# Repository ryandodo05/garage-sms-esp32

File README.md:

# Projet : Carte ESP32 + SIM7080G, pilotage d'une porte de garage par SMS

Carte PCB ESP32 avec module SIM7080G, relais et capteur ultrason, pour surveiller
et piloter une porte de garage par SMS.

Auteur : Ryan, https://ryan-dodo.be/Projet1.html

## Description

Le but du projet est de surveiller et piloter à distance plusieurs éléments de mon
domicile, principalement ma porte de garage. Le cœur de la carte est un ESP32,
complété par un module SIM7080G qui assure la communication cellulaire par SMS.

- **Porte de garage** : une broche de l'ESP32 est reliée à l'entrée du boîtier de
  gestion de la porte. Un SMS contenant « Garage » envoie une impulsion : si la
  porte est fermée, elle s'ouvre, et inversement.
- **Détection de voiture** : un capteur ultrason HC-SR04 (portée d'environ 5 mètres)
  est fixé au mur du garage. En réponse au SMS « Garage », il indique si une voiture
  est garée ou non.
- **Pilotage de charges** : deux relais permettent de commuter du 12 V. Comme la
  sortie de l'ESP32 ne fournit pas assez de tension ni de courant pour la bobine,
  chaque relais est commandé par un transistor et des résistances. Un SMS tel que
  « relai1 » active le relais 1, par exemple pour alimenter un spot LED.
- **Sécurité** : seuls les SMS envoyés depuis mon numéro de téléphone sont pris en
  compte. Tout message provenant d'un autre numéro est ignoré.

## Fonctionnalités

- Ouverture / fermeture de la porte de garage par SMS (impulsion sur broche dédiée)
- Détection de présence de voiture par capteur ultrason HC-SR04 (~5 m)
- Réponse par SMS : voiture garée ou garage libre
- Commande de deux relais 12 V par SMS (ex. « relai1 », « relai2 »)
- Commande des relais via transistors et résistances de base
- Filtrage des commandes : acceptées uniquement depuis mon numéro
- Communication cellulaire LTE-M avec le module SIM7080G
- PCB conçue entièrement par mes soins sous Eagle

## Caractéristiques

| Élément | Détail |
|---|---|
| Microcontrôleur | ESP32 |
| Communication | SIM7080G (LTE-M uniquement) |
| Sorties | 2 relais 12 V, pilotés par transistor |
| Capteur | HC-SR04, portée ~5 m |
| Commande porte | Impulsion sur broche dédiée |
| Conception | PCB dessinée par mes soins, fabriquée chez JLCPCB |

## Conception & fabrication

La carte a été entièrement conçue par mes soins sous Eagle (schéma, placement et
routage). Les fichiers Gerber ont été exportés puis la carte est fabriquée chez
JLCPCB, afin de limiter au maximum le risque de défaut de fabrication.

## Coûts indicatifs

| Élément | Prix |
|---|---|
| ESP32 | 13 € |
| Relais (unité) | 3 € |
| Module SIM7080G | 56 € |
| Reste des composants (transistors, résistances, capteur HC-SR04, connecteurs, PCB…) | 30 à 40 € |
| Abonnement SIM Orange (LTE-M), SMS illimités entrants et sortants | 15 € / mois |

La SIM doit être en LTE-M, car le module SIM7080G n'accepte que cette technologie.
Le forfait choisi permet d'envoyer et de recevoir autant de messages que souhaité.

## Vue 3D de la PCB

Voir la vue 3D interactive (chargement des Gerbers) sur
https://ryan-dodo.be/Projet1.html

<!--  -->

## Défis rencontrés

Le placement des composants RF du SIM7080G (antenne, découplage, masse) a demandé
une attention particulière pour limiter les interférences avec le reste de la carte.
La commande des relais 12 V a également nécessité l'ajout de transistors, car la
sortie de l'ESP32 ne suffit pas à alimenter directement les bobines.

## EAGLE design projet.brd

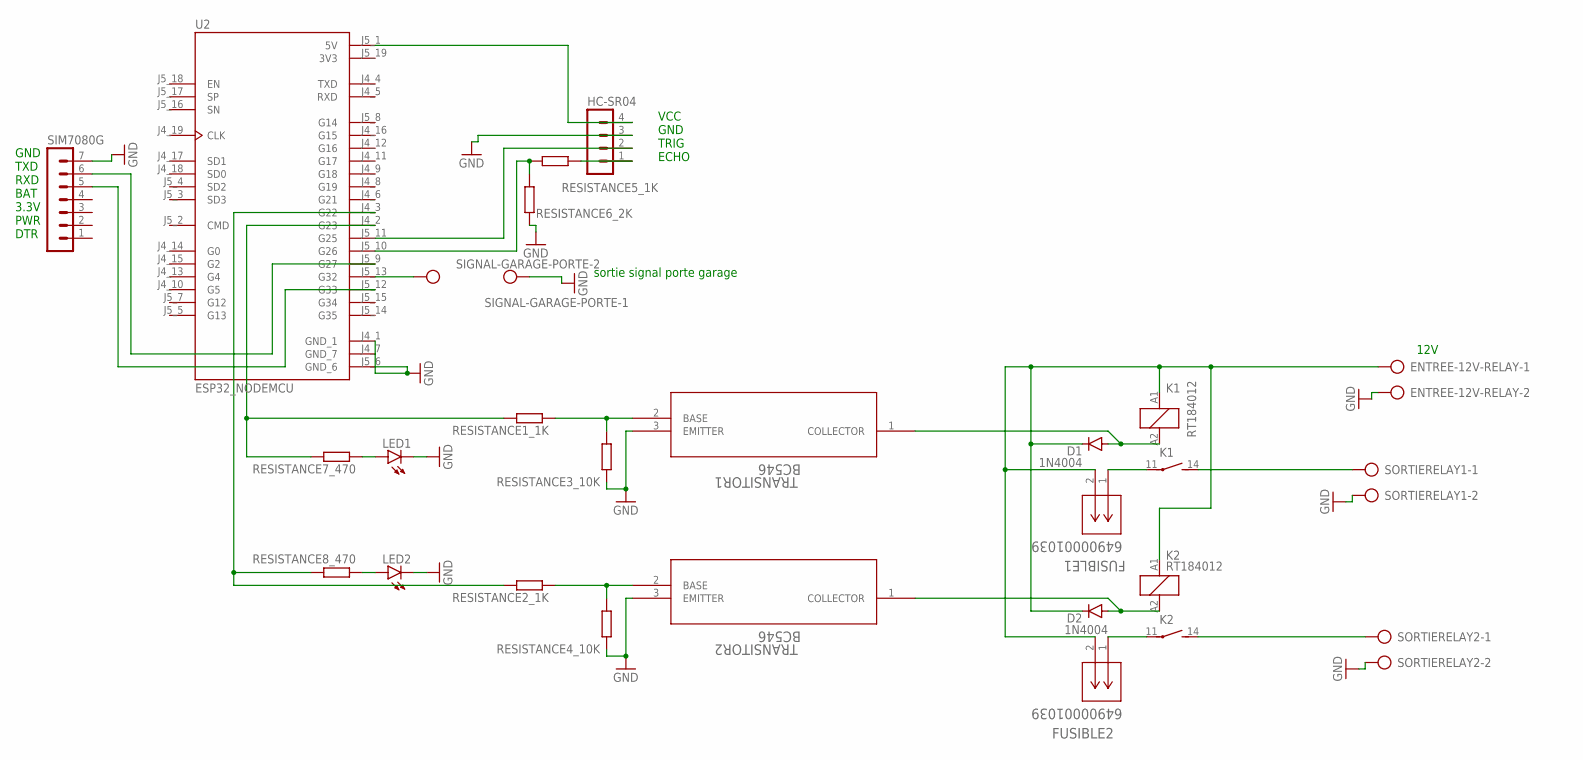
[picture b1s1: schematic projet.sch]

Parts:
D1, D2: 1N4004; DO41-10
ENTREE-12V-RELAY: AK300/2
FUSIBLE1, FUSIBLE2: 64900001039; CONN02_FUSEBLOCK_22P6X9_LTF
HC-SR04: MA04-1
K1, K2: RT184012; RT-N/O12A3.5
LED1, LED2: TLLY4400; LED3MM
RESISTANCE1_1K, RESISTANCE2_1K, RESISTANCE3_10K, RESISTANCE4_10K, RESISTANCE5_1K, RESISTANCE6_2K, RESISTANCE7_470, RESISTANCE8_470: R-EU_0204/7; 0204/7
SIGNAL-GARAGE-PORTE: AK300/2
SIM7080G: MA07-1
SORTIERELAY1, SORTIERELAY2: AK300/2
TRANSITOR1, TRANSITOR2: BC546; TO-92_ONS
U2: ESP32_NODEMCU; MODULE_ESP32_NODEMCU

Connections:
3V3: U2.J5_19 (3V3)
GND: ENTREE-12V-RELAY.2, HC-SR04.3, LED1.K (C), LED2.K (C), RESISTANCE3_10K.1, RESISTANCE4_10K.1, RESISTANCE6_2K.2, SIGNAL-GARAGE-PORTE.2, SIM7080G.7, SORTIERELAY1.2, SORTIERELAY2.2, TRANSITOR1.3 (EMITTER), TRANSITOR2.3 (EMITTER), U2.J4_1 (GND_1), U2.J4_7 (GND_7), U2.J5_6 (GND_6)
unnamed: RESISTANCE1_1K.1, RESISTANCE3_10K.2, TRANSITOR1.2 (BASE)
unnamed: SIGNAL-GARAGE-PORTE.1, U2.J5_13 (G32)
unnamed: RESISTANCE2_1K.1, RESISTANCE4_10K.2, TRANSITOR2.2 (BASE)
unnamed: RESISTANCE5_1K.1, RESISTANCE6_2K.1, U2.J5_10 (G26)
unnamed: LED2.A, RESISTANCE8_470.1
unnamed: D1.A, K1.A2 (2), TRANSITOR1.1 (COLLECTOR)
unnamed: K1.14 (S), SORTIERELAY1.1
unnamed: HC-SR04.2, U2.J5_11 (G25)
unnamed: D2.A, K2.A2 (2), TRANSITOR2.1 (COLLECTOR)
unnamed: HC-SR04.4, U2.J5_1 (5V)
unnamed: SIM7080G.5, U2.J5_12 (G33)
unnamed: K2.14 (S), SORTIERELAY2.1
unnamed: FUSIBLE1.1, K1.11
unnamed: FUSIBLE2.1, K2.11
unnamed: D1.C, D2.C, ENTREE-12V-RELAY.1, FUSIBLE1.2, FUSIBLE2.2, K1.A1 (1), K2.A1 (1)
unnamed: HC-SR04.1, RESISTANCE5_1K.2
unnamed: LED1.A, RESISTANCE7_470.1
unnamed: RESISTANCE2_1K.2, RESISTANCE8_470.2, U2.J4_3 (G22)
unnamed: RESISTANCE1_1K.2, RESISTANCE7_470.2, U2.J4_2 (G23)
unnamed: SIM7080G.6, U2.J5_9 (G27)

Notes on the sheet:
sortie signal porte garage
VCC GND TRIG ECHO
GND TXD RXD BAT 3.3V PWR DTR
12V

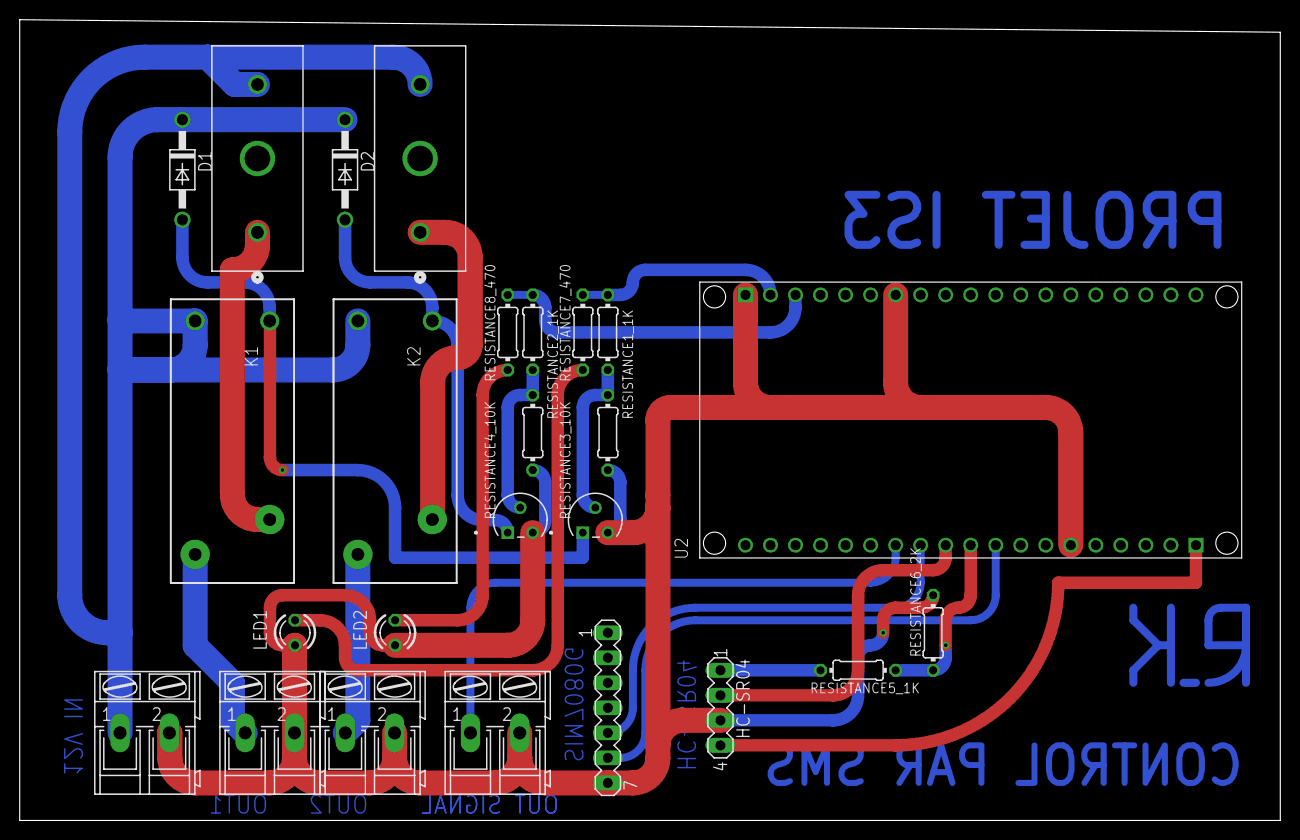
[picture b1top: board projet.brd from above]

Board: 2 copper layers, 127.9 x 81.3 mm, 25 parts (0 on the bottom side), 21 nets.

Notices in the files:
parts and their libraries:
COPYRIGHT: Copyright (C) 2026 Ultra Librarian. All rights reserved.
